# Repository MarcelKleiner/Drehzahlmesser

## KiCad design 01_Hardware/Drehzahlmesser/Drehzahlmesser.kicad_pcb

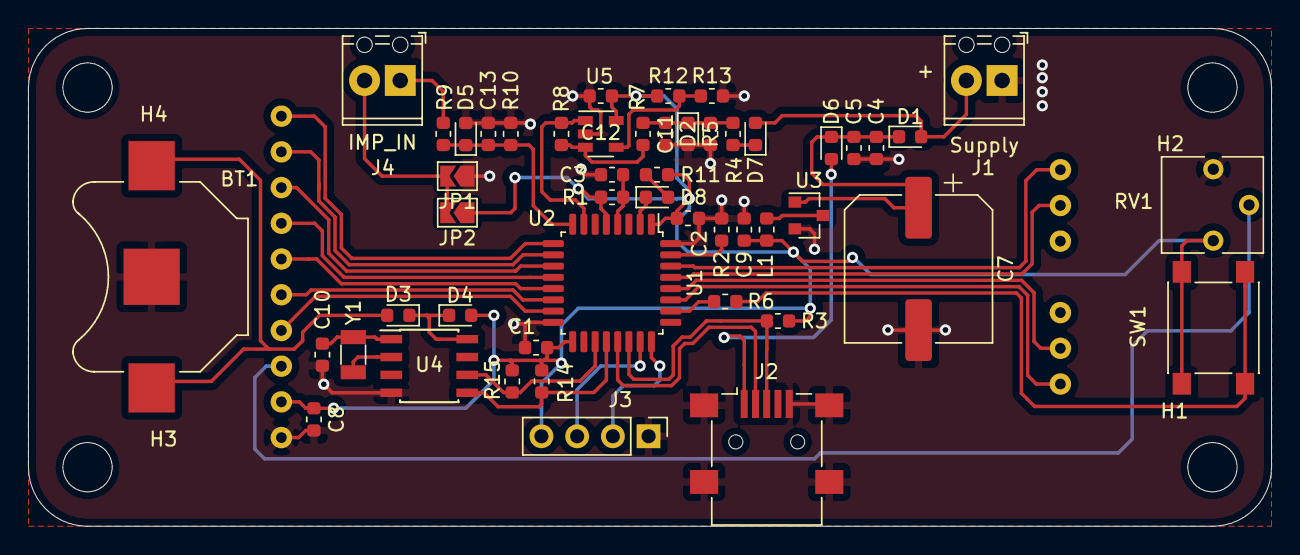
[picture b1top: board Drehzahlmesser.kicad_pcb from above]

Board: 2 copper layers, 88.4 x 35.4 mm, 55 parts (0 on the bottom side), 42 nets.

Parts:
BT1: Battery_Cell; BatteryHolder_Keystone_3000_1x12mm
C1, C2, C3, C8, C10, C12: 100n; C_0603_1608Metric
C4: 10u; C_0603_1608Metric
C5: 1u; C_0603_1608Metric
C7: 470u; CP_Elec_10x7.7
C9: C; C_0603_1608Metric
C11, C13: 10p; C_0603_1608Metric
D1, D3, D4, D6, D7: D_Schottky; D_0603_1608Metric
D2, D5: D_Zener; D_0603_1608Metric
D8: LED; LED_0603_1608Metric
H1, H2, H3, H4: MountingHole; MountingHole_3.5mm
J1, J4: Conn_01x02_Female; TerminalBlock_Phoenix_MPT-0,5-2-2.54_1x02_P2.54mm_Horizontal
J2: USB_B_Mini; USB_Mini-B_Lumberg_2486_01_Horizontal
J3: Conn_01x04_Male; PinHeader_1x04_P2.54mm_Vertical
JP1: JP_GND; SolderJumper-2_P1.3mm_Open_TrianglePad1.0x1.5mm
JP2: JP_VCC; SolderJumper-2_P1.3mm_Open_TrianglePad1.0x1.5mm
L1: 10uH; L_0603_1608Metric
R1, R2, R11: 100k; R_0603_1608Metric
R3, R6: 1.5k; R_0603_1608Metric
R4, R5, R9, R10: R; R_0603_1608Metric
R7: 1k; R_0603_1608Metric
R8: 4.7k; R_0603_1608Metric
R12, R13, R14, R15: 10k; R_0603_1608Metric
RV1: R_POT; Potentiometer_Vishay_T73YP_Vertical
SW1: SW_Push; SW_SPST_PTS645
U1: STM32L412K8Tx; LQFP-32_7x7mm_P0.8mm
U2: LCD_NHD-0108CZ; LCD_NHD_0108CZ
U3: AP7384; SOT-23
U4: PCF8563T; SOIC-8_3.9x4.9mm_P1.27mm
U5: OPA330xxDBV; SOT-23-5
Y1: Crystal; Crystal_SMD_3215-2Pin_3.2x1.5mm

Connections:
+3V3: C1.1, C2.1, C8.1, C9.1, C12.1, D4.2, J3.4, JP2.1, L1.2, R1.1, R3.1, R11.1, R12.1, R14.2, R15.1, RV1.1, SW1.2, U1.1, U1.5, U1.17, U2.2, U5.5
AC: D1.2, D7.2, J1.2
D+: J2.3, R3.2, U1.22
D-: J2.2, U1.21
DB0: U1.27, U2.11
DB1: U1.28, U2.12
DB2: U1.29, U2.13
DB3: U1.30, U2.14
DB4: U1.12, U2.7
DB5: U1.11, U2.8
DB6: U1.10, U2.9
DB7: U1.9, U2.10
E: U1.13, U2.6
GND: BT1.2, C1.2, C2.2, C3.2, C4.2, C5.2, C7.2, C8.2, C9.2, C10.2, C11.2, C12.2, C13.2, D2.2, D5.2, J1.1, J2.5, J2.6, J3.1, JP1.1, R2.1, R5.2, R10.2, R13.2, RV1.3, U1.16, U1.32, U2.1, U3.2, U4.4, U5.2
LED: D8.1, U1.2
unnamed: BT1.1, D3.2
unnamed: C3.1, R1.2, U1.4
unnamed: C4.1, C5.1, C7.1, D1.1, D6.1, U3.1
unnamed: C10.1, U4.1, Y1.1
unnamed: C11.1, D2.1, R4.2, R5.1, R7.1
unnamed: D3.1, D4.1, U4.8
unnamed: D7.1, R4.1
unnamed: D8.2, R11.2
unnamed: J4.1, R9.1
unnamed: J4.2, JP1.2, JP2.2
unnamed: L1.1, U3.3
unnamed: R2.2, U1.31
unnamed: R6.2, SW1.1
unnamed: R7.2, R8.1, U5.3
unnamed: R12.2, R13.1, U5.4
unnamed: RV1.2, U2.3
unnamed: U4.2, Y1.2
RPM: R8.2, U1.7, U5.1
RS: U1.15, U2.4
R_W: U1.14, U2.5
SCL: R15.2, U1.19, U4.6
SDA: R14.1, U1.20, U4.5
SW: R6.1, U1.26
SWCLK: J3.2, U1.24
SWDIO: J3.3, U1.23
VBUS: D6.2, J2.1
kmh: C13.1, D5.1, R9.2, R10.1, U1.8

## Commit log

2021-04-11 update layou
2021-06-13 hardware update
